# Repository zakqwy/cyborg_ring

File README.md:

# cyborg ring

cyborg ring is a cordwood-style bit of blinky jewelry powered by an ATtiny85 and a pair of size 10 Zn-air (hearing aide) batteries. The latest iteration includes several tension wires as well as other minor updates and has proven its durability to be sufficient to warrant a beta release. Note that this ring is difficult to make, still quite delicate, not waterproof (even if you conformal coat most of it), and somewhat uncomfortable. But it's also quite unique.
## license
cyborg ring is released under the terms of the Creative Commons Attribution-ShareAlike 4.0 license, available here: http://creativecommons.org/licenses/by-sa/4.0/.

The project recently received certification from the Open Source Hardware Association, US000141.

## project status

The ring works and seems to last at least a few weeks without breaking; having said that, the ring is still delicate and should be treated like a beta-release concept still in need of some polishing. By popular demand, I'll probably put together a CrowdSupply campaign for kits that will include good instructions, pre-programmed microcontrollers, and LED color / ring size choice. On the subject of size, this version is nominally equivalent to ring size 9. Practically, it's better as a 7 or 8 as the bare FR4 is a bit rough when worn too tight.
## build instructions
I did a live stream in October 2018 that shows a complete ring build start-to-finish. You can view an unedited recording of the stream [here](https://youtu.be/spNg8LhxJz0). I also made a brief video that just goes over the tools and materials, available [here](https://youtu.be/D9dDy7vboAA). These are both great starting points if you are new to the project.
### step zero: prepare thyself
This is a fun and challenging project. Building a ring can be frustrating, especially if you aren't used to working with tiny parts, but if you take your time it is eminently possible even if you are fairly new to soldering. Make sure you are comfortable, not overly caffeinated (as shaky hands make it quite tough), and try to avoid interruptions for the next few hours. Remember that you have extra parts, and even if you damage a PCB the replacements are quite cheap (although they may take a week or two to arrive in the mail).
### step one: source PCBs
Use a service like [OSHpark](https://oshpark.com/shared_projects/sZ3MaKA4) (or any other high-quality PCB vendor) to fabricate the boards. They should be routed with mousebites, 0.8mm (1/32") FR4, ENIG, double-sided. Note that some traces are a bit close to the PCB edge so you may need to try a few services or have your bodge wires handy:

If necessary, _carefully_ sand down the mouse bites after removing excess FR4. Make sure to wear suitable PPE (safety glasses, a dust mask, etc) and clean up when you are finished:

### step two: source all the parts
I did a short run of kits that were given away at the 2018 Supercon; if you got one, you already have all you need beyond the tools listed:

Otherwise, order the parts listed in bom.csv in the HARDWARE directory. I usually get parts from Digi-Key, but most large electronics distributors should have the parts. Make sure you buy 0508 resistors for the LEDs; they're a bit funky and substantially less common than 0805 devices (which you also need). And don't even _think_ about not ordering sufficient spares of _everything_.
### step three: assemble the resistor columns
You need six columns altogether. Four should be constructed from a pair of 10M 0805 resistors, marked '106', to give a total resistance of 20M. Two should be constructed from a pair of 0805 jumpers, marked '0'. To fabricate the columns, position the two resistors next to each other on a heat-resistant surface (such as a Teflon-jawed Stickvise):

Squeeze the two resistors together with a pair of tweezers. Make sure they are square to each other and don't squeeze so hard the resistors buckle up in the center; the column should be flat but firmly held:

Apply a bit of gel flux to the junction:

Touch your tinned soldering iron to the junction, allowing a bit of solder to flow around the joint:

The finished product should be straight and square, as seen here:

Repeat as needed until you have two jumper columns and four structural (10M + 10M) columns.
### step four: solder parts to individual ring halves
Identify the bottom half of the ring. This half has two round pads on the back, along with two rectangular pads for the switch. On the front, the ATtiny85 silkscreen has a tiny circle to indicate the location of Pin 1. It also says "cyborg ring" opposite the LEDs:

Start by soldering the QFN ATtiny85 to the PCB. You should carefully mount the board in a vise of some kind, or tape it to a work surface (such as an old bit of wood) so it doesn't move around. Use tweezers to orient the QFN so its ground pad faces the bottom part of the ring, and the outline lines up with the white silkscreen square. Be sure the notch on the ground pad, which indicates pin 1, is down and to the right:

Squeeze a healthy blob of gel flux onto the joint (not shown). Tin your soldering iron, keep your tweezers steady, confirm alignment one last time, and slide the iron tip across the joint to flow sufficient solder onto the pads. If you form any bridges, clean off the iron and gently dab it on the pads to remove excess solder:

The resultant joint should be shiny, convex, aligned front-to-back and side-to-side, and as vertical as you can manage. Examine this joint carefully, ideally with a loupe, and redo if necessary to fix problems:

Next, solder the six resistor columns to the ring. The two jumper columns guard the QFN, while the four structural columns live near the ring's corners (if round things had corners). Follow the same method as you did with the QFN: add a blob of flux, align the column with tweezers, tin your iron, and touch the hot iron tip to the joint to flow a bit of solder onto the pad and component:

Now solder all 0508 resistors to the appropriate pads on the top and bottom of the ring. Orient the resistors so their top edge is flush with the top of the ring. When you are done, the bottom half should look something like this:

Solder the battery tabs to the smaller of the round pads on the left side of each half of the ring. Orient the tabs so the battery can be inserted and removed from the bottom of the ring after assembly. Again, add flux to the pad, align and hold the part, and touch the joint with a tinned iron tip to flow sufficient solder into the joint. Note that the tab in this image is an older version; your parts are sturdier but otherwise similar (and your QFN is straighter than the one in this picture):

### step five: join the two ring halves
This is the most challenging part of the ring construction. The components are all in a delicate state (especially the brittle resistor columns), and the two halves need to be aligned within around 100 microns to ensure the QFN pads all land properly. I demonstrated this step on stage at the 2018 Supercon; [the video](https://www.youtube.com/watch?v=hiBTvdMfvWo) isn't great but hopefully the methodology comes through. I still need to pull together good images showing this part in action, but it's tough to photograph as both hands tend to be busy.

Pick up the bottom ring half (the part with most of the components) with your thumb and forefinger. Place the top ring half over the bottom half, gently squeezing the two PCBs together between your fingers. Adjust your grip so that the two boards are aligned, and ensure that there is some pressure holding them together; any gaps between the components and the PCB will be difficult to fix with solder. As you hold the PCB, notice how much fine control you have over component alignment by sliding your thumb and forefinger relative to each other. Practice getting the QFN pads perfectly in line and holding them that way for a few seconds. Keep an eye on the alignment of the two furthest structural columns; if all three of these joints are in line, the other resistors will fall into place as well.

When you are comfortable with your grip on the PCBs, add a blob of flux to the five unsoldered QFN pads, tin your iron, check alignment one final time, and swipe the iron tip across the pads to flow solder into the joint. Be sure to hold the boards steady during this process; don't let go until the iron has been off the joint for a few seconds, as you must ensure the solder is completely cool or you'll get a cold joint.

As soon as the solder on the QFN joint solidifies, start treating the ring with even greater care. The five pads holding the top PCB are tiny and easily ripped off. Without putting the ring down, add gel flux to the six structural resistor columns, re-tin your iron tip, and touch the six pads in sequence to flow solder into the joints. Now you can put the ring down and inspect your work; the ring is still too delicate to wear (which we will address next), but it shouldn't spontaneously disassemble if left on the workbench until the next morning.
### step six: install reinforcing wires
The major design update between the two hardware revisions to date added eight tension wires. The original ring was incredibly weak in tension or shear, as the resistors would easily lose their solder caps. Think of the columns as un-reinforced concrete: they're pretty decent in compression, but need a bit of help for real-world applications.

Each ring PCB has eight tiny plated holes designed for stripped 30 AWG wire wrap wire. The clearance is tight, so inserting the wire through both holes can be a trial-and-error process. Generally, if you kink or bend the wire in an attempt, you are better off clipping the wire back until you have a fresh straight section to work with. Some of the holes are marked here:

One at a time, blob flux onto the wire and holes and apply solder as you did with the other components. As you secure each joint, clip the wires flush. If the clipped wire is sharp, dab it with a tinned iron to add a tiny bit of additional solder to round off the joint.

Now you can wear the ring. But you will probably want to install the rest of the components first, as it's quite a bit more interesting to see when the LEDs work.

### step seven: install the LEDs
The LEDs straddle the gap between the 0508 resistors at the top of each ring PCB. This works because the resistors are 1.2 mm wide each, and 0603 LEDs are 1.6 mm wide. 1.2 + 1.6 + 1.2 = 4, and it means the LEDs are nicely centered. However, they are quite delicate and dependent on nominal tolerances, so they don't always fit quite right, and can easily break if you throw an unprotected ring in your backpack for a month (as I did on the broken-but-re-LED-able ring shown on the right here):

LED polarity should always be confirmed on the LED datasheet, but in most cases the cathode (negative) terminal of a component can be identified by the black dot visible through the epoxy package. Install the LEDs according to this diagram:

Don't worry if you get all of them backwards. The LEDs are Charlieplexed, so they will still light up but will be in a funky order. You can fix them, or you can fix the code. Just make sure the polarities alternate from one to the next.

Secure the ring upright. To install the LEDs, dab a bit of gel flux on the free pads of the 0508 resistors and the LED terminals. Hold each LED in sequence in its appropriate place and touch your tinned iron to the terminal to flow solder into the joint. This may take a bit of practice and rework, so take your time. Be sure to solder both sides of each LED before you move on to the next.
### step eight: final components and ground jumper
The ring has two components that must be soldered in traditional fashion to the PCBs. The 0402 bypass capacitor should be soldered to the top PCB, while the side-mounted switch should be soldered to the bottom PCB. The switch pads aren't terribly generous, so a good strategy is to tin the pads and switch terminals, deflux the whole ring with isopropyl alcohol (as the switch isn't sealed), and secure the switch by reflowing the pads from above.

Remember how the QFN ATtiny85 (/45/25) is great for cordwood because all of the pins are broken out on two sides of the QFN? Well .. not _quite_ all of the pins. You have to jumper in the ground connection. To do this, blob some flux onto the ground pad on the back of the chip and touch it with a tinned iron to flow on some solder. Then, tack a fluxed length of wire wrap wire onto the blob, being careful to avoid shorting the wire against any pins. Solder the other end of the wire to the resistor jumper column _opposite_ the ATtiny's Pin 1 indicator, as shown here:

You can also use the position of the switch as a guide, following the image above.
### step nine: programming
The ring firmware (/FIRMWARE) runs on an ATtiny85 microcontroller, but can easily work with a -25 or -45 as well (these devices simply have less flash memory, not a problem for our tiny program). If you use an ATtiny25 or ATtiny45, be sure to change the DEVICE line of the Makefile as required.

You can program the ring with any suitable AVR programmer: a USBtinyISP, an Arduino, or one of Atmel's many official devices. Using these specific devices is outside the scope of these instructions; a good starting point is Adafruit's fantastic guide for their USBtinyISP, available [here](https://learn.adafruit.com/usbtinyisp). Connect your programmer of choice to the following pads on the ring:

The pads are 0.1" spaced so you _can_ build a clever pinchy programmer rig out of perfboard and pogo pins, like this:

The programming rig works well enough, but it's fussy to get aligned so I usually just tack wires onto the pads. The current firmware zips the LEDs sequentially three times, then puts the microcontroller to sleep. Battery life should be in the 6-8 weeks range and is probably chemistry-limited rather than related to current draw (unless you play with the ring _constantly_)

Optionally, you can now coat the exposed parts of the ring with silicone modified conformal coating. The ring won't be waterproof, but it will be a bit better protected.

### step ten: what to do if your ring doesn't work
I have built five of these rings as of November 2018, and I had to perform at least some rework on three of them before they would accept a program. So don't fret if you get an avrdude error! A few recommended troubleshooting steps:
* Double-check the programming connections against the diagram shown in step 9. While you're at it, make sure your programmer is connected and working (and providing power, if you haven't installed batteries yet)!
* Make sure the ATtiny is oriented correctly vs the pin 1 indicator. Seriously, I messed this up _several times_ but was able to recover using hot air in all cases.
* Re-examine the QFN solder joints with a loupe. If the chip is lifted or misaligned at all, one or more of the fillets may not contact the pads and it's really tough to see without 10x or better magnification. If you see some suspect solder joints, clean them with a bit of isopropyl alcohol, add flux, and gently sweep them with a lightly tinned iron tip.
* Make sure you didn't swap the resistor columns! The two on either side of the ATtiny should be jumpers, while the other four should be 10M + 10M.

Finally, please don't hesitate to get in touch if you want a second set of eyes on your work. The best route to contact me for help with your build is via [Twitter](https://twitter.com/zakqwy). If you aren't on that platform, you can also submit a GitHub Issue. Make sure to include close-up pictures!
## known builds
Building a cyborg ring and willing to share your process? Send me a link and I'll add it here.

[F0cks' build](https://blog.f0cks.net/projects/Cyborg-ring/), remixed to ring size 6.5-7 in Eagle and used for a proposal!

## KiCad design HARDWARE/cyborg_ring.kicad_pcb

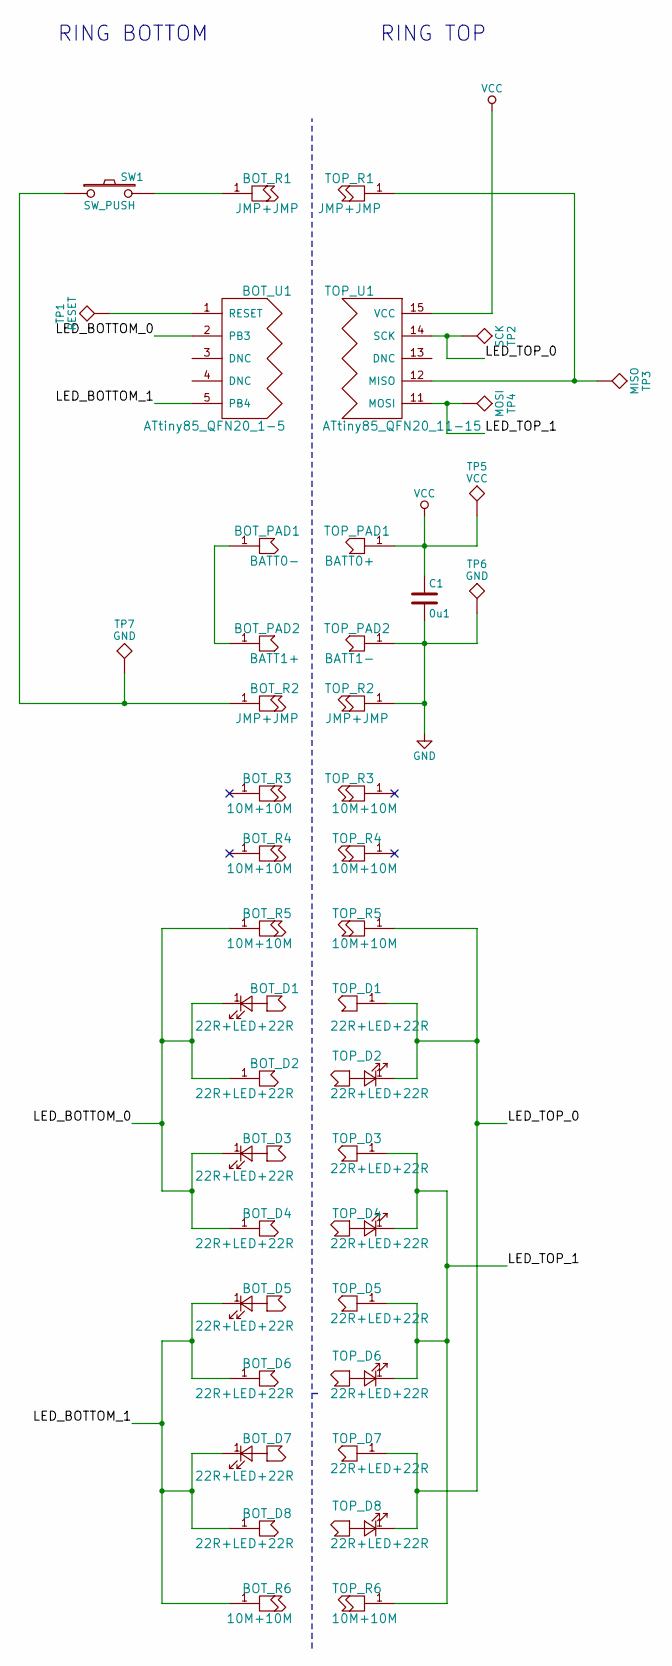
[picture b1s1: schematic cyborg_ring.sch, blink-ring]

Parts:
BOT_D1, BOT_D2, BOT_D3, BOT_D4, BOT_D5, BOT_D6, BOT_D7, BOT_D8: 22R+LED+22R; ZF_SMD_0508_CORD
BOT_PAD1: BATT0-; ZF_BATT_AC10E_NEG; Mfr Part # 1447360-8
BOT_PAD2: BATT1+; ZF_BATT_AC10E_POS
BOT_R1, BOT_R2: JMP+JMP; ZF_SMD_0805_CORD
BOT_R3, BOT_R4, BOT_R5, BOT_R6: 10M+10M; ZF_SMD_0805_CORD
BOT_U1: ATtiny85_QFN20_1-5; ZF_IC_MLF20-050_CORD_1-5; Mfr Part # ATTINY85-20MUR
C1: 0u1; ZF_SMD_NonPol_0402_cap
SW1: SW_PUSH; ZF_SW_B3U; Mfr Part # B3U-3000P
TOP_D1, TOP_D2, TOP_D3, TOP_D4, TOP_D5, TOP_D6, TOP_D7, TOP_D8: 22R+LED+22R; ZF_SMD_0508_CORD
TOP_PAD1: BATT0+; ZF_BATT_AC10E_POS
TOP_PAD2: BATT1-; ZF_BATT_AC10E_NEG; Mfr Part # 1447360-8
TOP_R1, TOP_R2: JMP+JMP; ZF_SMD_0805_CORD
TOP_R3, TOP_R4, TOP_R5, TOP_R6: 10M+10M; ZF_SMD_0805_CORD
TOP_U1: ATtiny85_QFN20_11-15; ZF_IC_MLF20-050_CORD_11-15; Mfr Part # ATTINY85-20MUR
TP1: RESET; ZF_CONN_1-2_pad
TP2: SCK; ZF_CONN_1-2_pad
TP3: MISO; ZF_CONN_1-2_pad
TP4: MOSI; ZF_CONN_1-2_pad
TP5: VCC; ZF_CONN_1-2_pad
TP6, TP7: GND; ZF_CONN_1-2_pad

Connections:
/LED_BOTTOM_0: BOT_D1.1, BOT_D2.1, BOT_D3.1, BOT_D4.1, BOT_R5.1, BOT_U1.2 (PB3)
/LED_BOTTOM_1: BOT_D5.1, BOT_D6.1, BOT_D7.1, BOT_D8.1, BOT_R6.1, BOT_U1.5 (PB4)
/LED_TOP_0: TOP_D1.1, TOP_D2.1, TOP_D7.1, TOP_D8.1, TOP_R5.1, TOP_U1.14 (SCK), TP2.1
/LED_TOP_1: TOP_D3.1, TOP_D4.1, TOP_D5.1, TOP_D6.1, TOP_R6.1, TOP_U1.11 (MOSI), TP4.1
GND: C1.2, TOP_PAD2.1, TOP_R2.1, TP6.1
unnamed: BOT_PAD1.1, BOT_PAD2.1
unnamed: BOT_R1.1, SW1.2
unnamed: BOT_R2.1, SW1.1, TP7.1
unnamed: BOT_U1.1 (RESET), TP1.1
unnamed: TOP_R1.1, TOP_U1.12 (MISO), TP3.1
VCC: C1.1, TOP_PAD1.1, TOP_U1.15 (VCC), TP5.1

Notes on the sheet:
RING BOTTOM
RING TOP

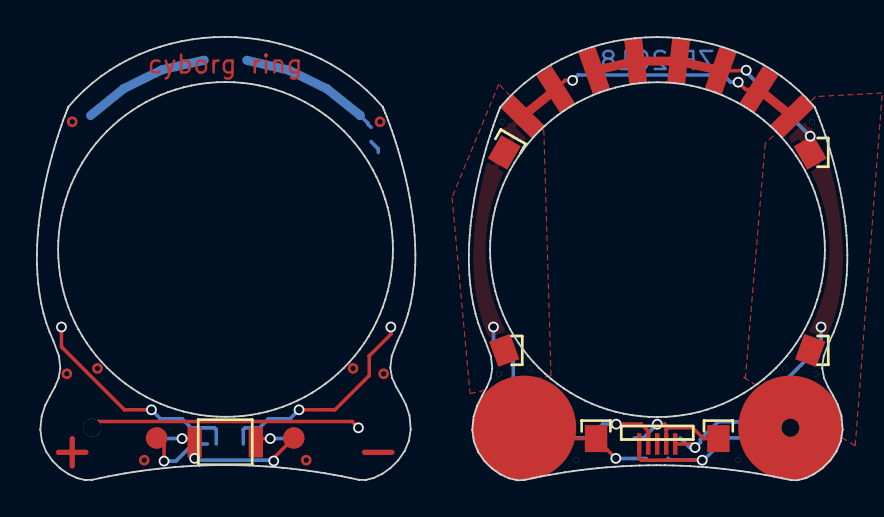
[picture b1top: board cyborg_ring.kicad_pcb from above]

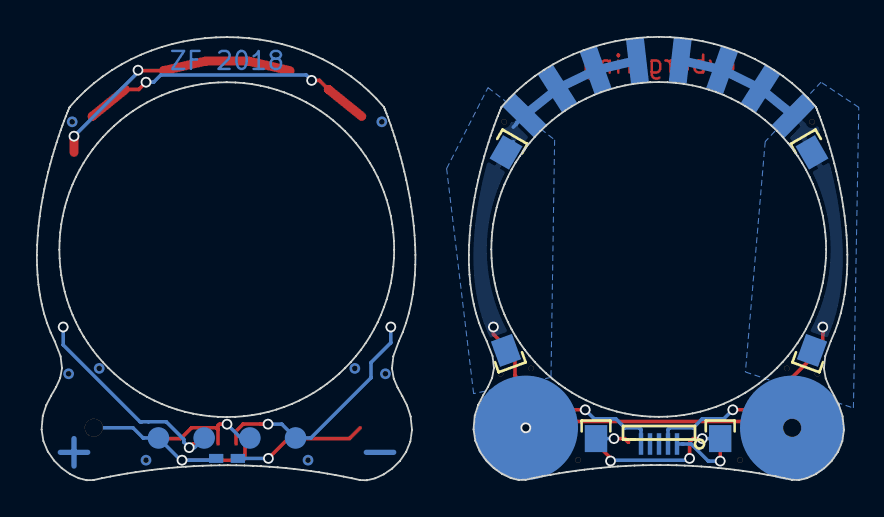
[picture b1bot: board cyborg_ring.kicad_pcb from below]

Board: 2 copper layers, 45.0 x 24.6 mm, 42 parts (22 on the bottom side), 11 nets.

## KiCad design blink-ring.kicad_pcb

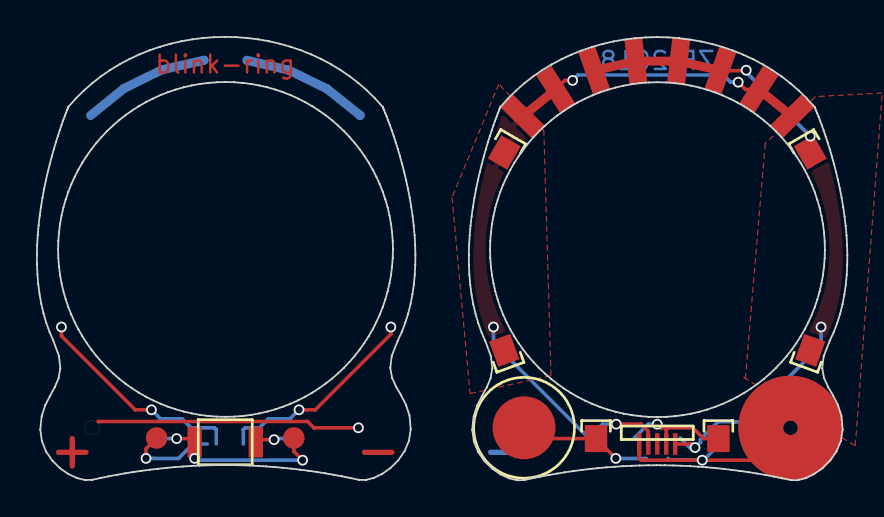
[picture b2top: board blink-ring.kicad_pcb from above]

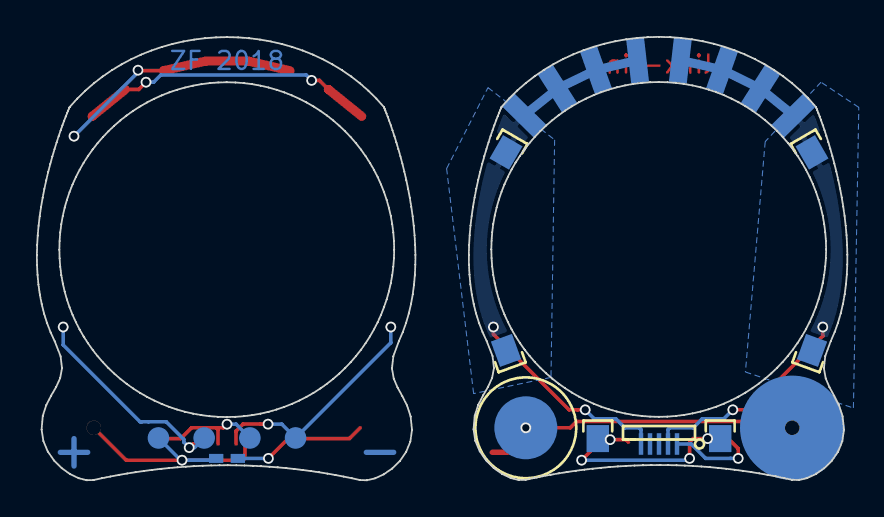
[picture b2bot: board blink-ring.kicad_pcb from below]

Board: 2 copper layers, 45.0 x 24.6 mm, 34 parts (18 on the bottom side), 11 nets.

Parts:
C1: C; ZF_SMD_NonPol_0402_cap
D1, D2, D3, D4, D5, D6, D7, D8: ZF_SMD_0805_CORD; ZF_SMD_0508_CORD
NA1, NA2: SW_JMP; ZF_SMD_0805_CORD
NA3, NA4: JMP_GND; ZF_SMD_0805_CORD
R1: BATT0-; ZF_BATT_AC10E_NEG
R2: BATT0+; ZF_BATT_AC10E_POS
R3: BATT1+; ZF_BATT_AC10E_POS
R4: BATT1-; ZF_BATT_AC10E_NEG
R5, R6, R7, R8, R9, R10, R11, R12: ZF_SMD_0805_CORD; ZF_SMD_0508_CORD
SW1: SW_PUSH; ZF_SW_B3U
TP1: RESET; ZF_CONN_1-2_pad
TP2: SCK; ZF_CONN_1-2_pad
TP3: MISO; ZF_CONN_1-2_pad
TP4: MOSI; ZF_CONN_1-2_pad
TP5: VCC; ZF_CONN_1-2_pad
TP7: GND; ZF_CONN_1-2_pad
U1: ATtiny85_QFN20_1-5; ZF_IC_MLF20-050_CORD_1-5
U2: ATtiny85_QFN20_11-15; ZF_IC_MLF20-050_CORD_11-15

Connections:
/LED_BOTTOM_0: D1.1, D3.1, R6.1, R8.1, U1.2
/LED_BOTTOM_1: D5.1, D7.1, R10.1, R12.1, U1.5
/LED_TOP_0: D2.1, D8.1, R5.1, R11.1, TP2.1, U2.14
/LED_TOP_1: D4.1, D6.1, R7.1, R9.1, TP4.1, U2.11
GND: C1.2, NA4.1, R4.1
unnamed: NA1.1, SW1.2
unnamed: NA2.1, TP3.1, U2.12
unnamed: NA3.1, SW1.1, TP7.1
unnamed: R1.1, R3.1
unnamed: TP1.1, U1.1
VCC: C1.1, R2.1, TP5.1, U2.15

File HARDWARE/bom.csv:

Ref,Qty,Value,Link,Mfr,Mfr Part #,Package,RoHS,Subs Allowed
BOT_PAD1 TOP_PAD2 ,2,BATT0- BATT1-,https://www.digikey.com/product-detail/en/te-connectivity-am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,TE Connectivity,1447360-8,SMT,Yes,No
BOT_R2 TOP_R2 TOP_R1 BOT_R1 ,2,JMP+JMP, , , ,R0805+R0805,Yes,Yes
BOT_R6 TOP_R6 BOT_R5 TOP_R5 BOT_R4 TOP_R4 TOP_R3 BOT_R3 ,4,10M+10M, , , ,R0805+R0805,Yes,Yes
BOT_U1 TOP_U1,1,ATtiny85_QFN20_1-5,https://www.digikey.com/product-detail/en/microchip-technolo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,Atmel/Microchip,ATTINY85-20MUR ,QFN20-0.5,Yes,No
C1 ,1,0u1, , , ,C0402,Yes,Yes
SW1 ,1,SW_PUSH,https://www.digikey.com/product-detail/en/omron-electronics-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,Omron Electronics,B3U-3000P,SMT,Yes,No
TOP_D1 BOT_D1 BOT_D2 TOP_D2 TOP_D3 BOT_D3 BOT_D4 TOP_D4 TOP_D5 BOT_D5 BOT_D6 TOP_D6 TOP_D7 BOT_D7 BOT_D8 TOP_D8 ,8,22R+LED+22R,https://www.digikey.com/product-detail/en/rohm-semiconductor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, , ,R0508+LED0603+R0508,Yes,No
TOP_PAD2 ,1,BATT1-,https://www.digikey.com/product-detail/en/te-connectivity-am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,TE Connectivity,1447360-8,SMT,Yes,No
,,,,,,,,
,,,,,,,,
,,,,,,,,
,,,,,,,,
BOM made with KICAD_BOM_WIZARD (https://github.com/HashDefineElectronics/KiCad_BOM_Wizard.git),,,,,,,,
Generated Thu 24 May 2018 09:12:32 AM CDT,,,,,,,,

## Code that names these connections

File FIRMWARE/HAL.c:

/* 

Released under the terms of the MIT License.

The MIT License (MIT)
Copyright (c) 2016 by Zach Fredin
Permission is hereby granted, free of charge, to any person obtaining a copy of this software and associated documentation files (the "Software"), to deal in the Software without restriction, including without limitation the rights to use, copy, modify, merge, publish, distribute, sublicense, and/or sell copies of the Software, and to permit persons to whom the Software is furnished to do so, subject to the following conditions:

The above copyright notice and this permission notice shall be included in all copies or substantial portions of the Software.

THE SOFTWARE IS PROVIDED "AS IS", WITHOUT WARRANTY OF ANY KIND, EXPRESS OR IMPLIED, INCLUDING BUT NOT LIMITED TO THE WARRANTIES OF MERCHANTABILITY, FITNESS FOR A PARTICULAR PURPOSE AND NONINFRINGEMENT. IN NO EVENT SHALL THE AUTHORS OR COPYRIGHT HOLDERS BE LIABLE FOR ANY CLAIM, DAMAGES OR OTHER LIABILITY, WHETHER IN AN ACTION OF CONTRACT, TORT OR OTHERWISE, ARISING FROM, OUT OF OR IN CONNECTION WITH THE SOFTWARE OR THE USE OR OTHER DEALINGS IN THE SOFTWARE.	

Charlieplexing!

PB3		LED_BOTTOM_0
PB4		LED_BOTTOM_1
PB2		LED_TOP_0
PB0		LED_TOP_1
PB1		Switch (pull up)

					  |----|<D0----|
				 |----|			   |--------------------|	
				 |	  |----D1>|----|					|
LED_BOTTOM_0 ----|										|----LED_TOP_0
				 |    |----|<D2----|	 				|
				 |----|			   |----|				|
					  |----D3>|----|	|		 		|
										|				|
										|----LED_TOP_1	|
										|				|
					  |----|<D4----|	|				|
				 |----|			   |----|				|
				 |	  |----D5>|----|					|
LED_BOTTOM_1 ----|										|
				 |    |----|<D6----|		 			|
				 |----|			   |--------------------|	 
					  |----D7>|----|		 





*/

#include <avr/io.h>
#include <avr/interrupt.h>
#include "HAL.h"

void SystemInit(void) {
	DDRB = 0; //set everything to an input for now
	PORTB |= (1<<PB1); //switch pullup

	// set up tick timer:
	TCCR0A |= (1<<WGM01); //CTC at OCR0A
	TCCR0B |= ((1<<CS02) | (1<<CS00)); //clk/1024
	OCR0A = 30; //sets tick to ~1ms
	TIMSK |= (1<<OCIE0A); //output compare match 0A interrupt enable
	GIMSK |= (1<<PCIE); //pin change interrupt enable
	PCMSK |= (1<<PCINT1);
	sei();
}

void illuminateLED(uint8_t LED) {
	//	PB3		LED_BOTTOM_0
	//	PB4		LED_BOTTOM_1
	//	PB2		LED_TOP_0
	//	PB0		LED_TOP_1

	DDRB = 0;
	PORTB &= ~((1<<PB0) | (1<<PB2) | (1<<PB3) | (1<<PB4));
	switch(LED) {
		case 0:
			DDRB |= ((1<<PB3) | (1<<PB2));
			PORTB &= ~(1<<PB2);
			PORTB |= (1<<PB3);
			break;
			
		case 1:
			DDRB |= ((1<<PB3) | (1<<PB2));
			PORTB &= ~(1<<PB3);
			PORTB |= (1<<PB2);
			break;

		case 2:
			DDRB |= ((1<<PB3) | (1<<PB0));
			PORTB |= (1<<PB3);
			PORTB &= ~(1<<PB0);
			break;

		case 3:
			DDRB |= ((1<<PB3) | (1<<PB0));
			PORTB &= ~(1<<PB3);
			PORTB |= (1<<PB0);
			break;

		case 4:
			DDRB |= ((1<<PB4) | (1<<PB0));
			PORTB |= (1<<PB4);
			PORTB &= ~(1<<PB0);
			break;

		case 5:
			DDRB |= ((1<<PB4) | (1<<PB0));
			PORTB &= ~(1<<PB4);
			PORTB |= (1<<PB0);
			break;
	
		case 6:
			DDRB |= ((1<<PB4) | (1<<PB2));
			PORTB &= ~(1<<PB2);
			PORTB |= (1<<PB4);
			break;

		case 7:
			DDRB |= ((1<<PB4) | (1<<PB2));
			PORTB |= (1<<PB2);
			PORTB &= ~(1<<PB4);
			break;
	}
}

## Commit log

2017-12-26 initial commit. first rev schematic, start of pcb.
2018-01-02 finalized PCB outline and layout. ordered first rev.
2018-01-15 assembled board and bodged together some demo firmware. needs a few pcb tweaks but everything works..
2018-02-02 new PCB rev. added reinforcements, changed battery contact, fixed open LED trace
2018-05-17 localized schematic symbols. changed name. minor formatting changes.
2018-05-17 added readme, license, and picture
2018-05-17 minor README.md updates
2018-05-17 updated bom.csv. minor README.md updates. added a few images.
2018-05-24 added 10M+10M R0805+R0805 reinforcement resistors to BOM and schematic. updated component references on schematic, BOM, and layout to start with 'BOT_' or 'TOP_' for cordwood-style installations. min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
2018-06-04 added programming diagram. updated README.md with examples and OSHpark order link.
2018-11-03 fixed error
2018-11-07 documentation updates
2018-11-07 more README.md updates
2018-11-07 more README.md updates. build instructions good for now.. ?
2018-11-07 README.md updates
2018-11-14 added ground jumper diagram and instructions. added 'what to do if your ring doesn't work' section.

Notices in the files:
HARDWARE/cyborg_ring.sch:
License: CC-BY-SA 4.0
(c) copyright 2017 zach fredin
